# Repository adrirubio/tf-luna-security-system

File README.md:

# TF-Luna Security System
**Full Design Process**: [Blueprint Project](https://blueprint.hackclub.com/projects/7234)

An evolution of my Arduino-based security system that uses a TF-Luna LiDAR sensor to detect when someone passes through a bedroom door, triggering the ESP32-CAM to capture a photo of the intruder.

The system is built around a Freenove ESP32-S3-WROOM-1, which communicates with the TF-Luna over I2C to establish a baseline distance and detect motion. When an intruder is detected, the onboard camera captures an image and sends it to Home Assistant via Wi-Fi. A green LED indicates power status while a red LED flashes to signal an intruder alert. The entire system runs off a power bank and is housed in a custom 3D-printed case mounted with a custom carrier PCB, making it a compact, self-contained DIY security setup with future plans for AI-based person identification.

## Features

- **Intruder Detection:** Real-time motion detection using a TF-Luna LiDAR sensor with a focused 2-degree beam
- **Automatic Photo Capture:** ESP32-CAM captures an image when an intruder is detected passing through the door
- **Home Assistant Integration:** Sends captured images and alerts directly to Home Assistant over Wi-Fi
- **LED Indicators:** Green LED for power status, red LED flashes on intruder detection
- **I2C Communication:** Reliable sensor communication at 100Hz with the TF-Luna
- **Custom PCB:** Single carrier board designed in KiCad and manufactured by JLCPCB
- **Custom 3D Printed Case:** Designed in FreeCAD with mounting pillars and cutouts for all components
- **Power Bank Powered:** Runs off a standard power bank for easy and flexible placement
- **Autonomous Operation:** Runs continuously without manual interaction
- **Future AI Integration:** Planned AI-based identification to recognize the homeowner

## Hardware/BOM

| Component | Qty | Type |
|-----------|-----|------|
| Freenove ESP32-S3-WROOM-1 | 1 | Controller |
| TF-Luna LiDAR Sensor | 1 | LiDAR Sensor |
| microSD Card (32GB) | 1 | Storage |
| Custom Carrier PCB | 1 | PCB |
| Custom 3D Printed Case | 1 | Enclosure |
| Power Bank | 1 | Power |
| USB-A to USB-C Cable | 1 | Cable |
| Mounting Hardware (Assorted Screws) | 1 | Hardware |

## CAD Screenshots

| CAD Assembly (Front View)| CAD Assembly (Top View) |
|--------------------------|-------------------------|
|  |  |

| 3D Case (Front View) | 3D Case (Side View) |
|----------------------|---------------------|
|  |  |

## PCB Screenshots

| PCB Layout |
|-------------------------------|
|  |

| PCB 3D View (Front) | PCB 3D View (Back) |
|----------------------|---------------------|
|  |  |

## Usage
Mount the system above your bedroom door using the 3D-printed case. The TF-Luna LiDAR sensor establishes a baseline distance to the floor and continuously monitors for changes. When someone passes through the doorway, the sensor detects the distance change and triggers the ESP32-CAM to capture a photo. The image is then sent to Home Assistant over Wi-Fi, and the red LED flashes to indicate an intruder was detected. The green LED stays on to confirm the system is powered and running.

## TF-Luna Security System In Action

| Complete Assembly (Side View)|
|------------------------------|
|  |

| Complete Assembly (PCB and Case View) | Complete Assembly (Back View) |
|---------------------------------------|-------------------------------|
|  |  |

### Security System Demo
<a href="https://github.com/adrirubio/tf-luna-security-system/raw/main/demo/video/security-system-demo.mp4">Click here to download the security system demo video (MP4)</a>

### YouTube Demo
[Watch the demo on YouTube](https://youtu.be/43d7Ib5dUhA)

## License

MIT License

---

> GitHub [@adrirubio](https://github.com/adrirubio) &nbsp;&middot;&nbsp;

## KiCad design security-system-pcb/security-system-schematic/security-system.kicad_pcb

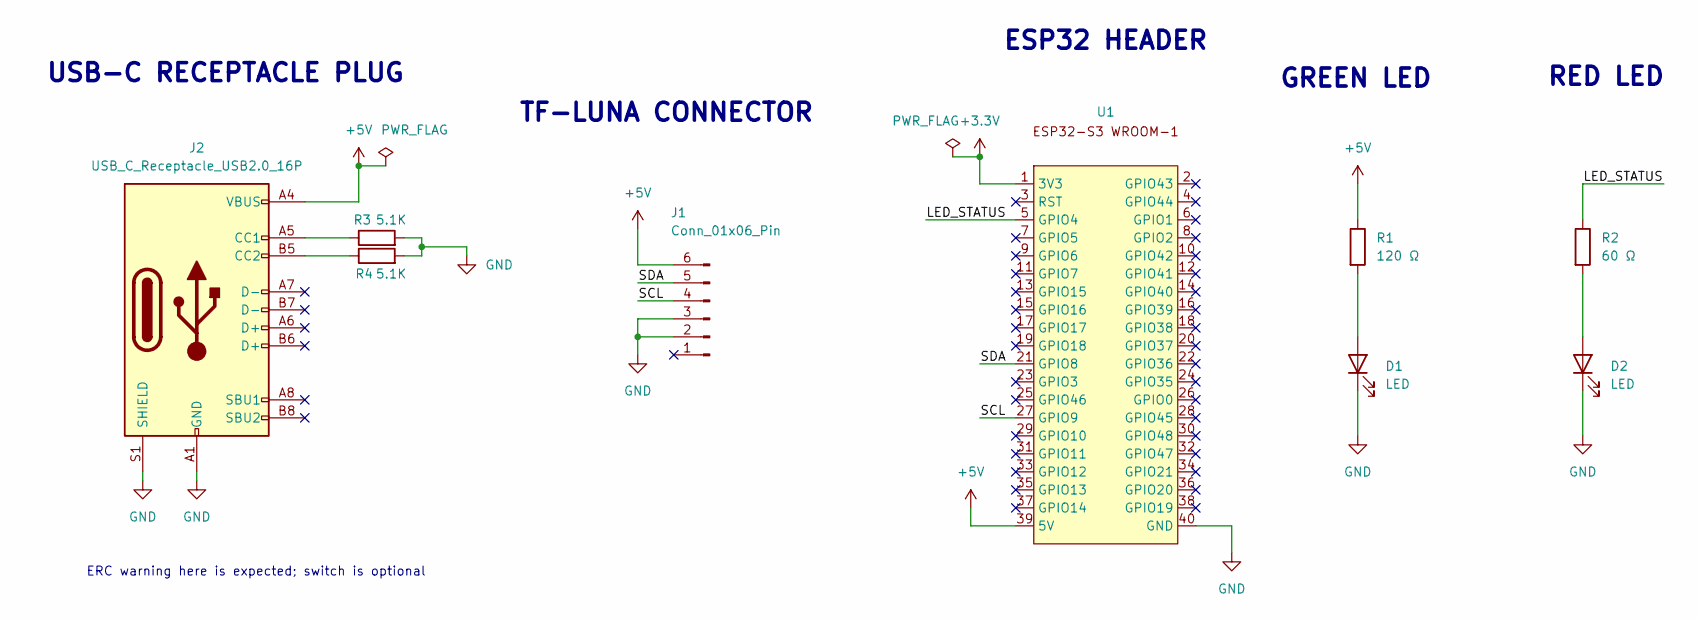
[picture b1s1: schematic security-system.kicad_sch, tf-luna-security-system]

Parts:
D1, D2: LED; LED_D5.0mm
J1: Conn_01x06_Pin; Molex_PicoBlade_53047-0610_1x06_P1.25mm_Vertical
J2: USB_C_Receptacle_USB2.0_16P; USB_C_Receptacle_GCT_USB4105-xx-A_16P_TopMnt_Horizontal
R1: 120 Ω; R_Axial_DIN0207_L6.3mm_D2.5mm_P7.62mm_Horizontal
R2: 60 Ω; R_Axial_DIN0207_L6.3mm_D2.5mm_P7.62mm_Horizontal
R3, R4: 5.1K; R_Axial_DIN0207_L6.3mm_D2.5mm_P7.62mm_Horizontal
U1: ESP32-Header; esp32-header

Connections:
+3.3V: U1.1 (3V3)
+5V: J1.6, J2.A4 (VBUS), J2.A9 (VBUS), J2.B4 (VBUS), J2.B9 (VBUS), R1.1, U1.39 (5V)
/LED_STATUS: R2.1, U1.5 (GPIO4)
/SCL: J1.4, U1.27 (GPIO9)
/SDA: J1.5, U1.21 (GPIO8)
GND: D1.1 (K), D2.1 (K), J1.2, J1.3, J2.A1 (GND), J2.A12 (GND), J2.B1 (GND), J2.B12 (GND), J2.S1 (SHIELD), R3.2, R4.2, U1.40 (GND)
unnamed: D1.2 (A), R1.2
unnamed: D2.2 (A), R2.2
unnamed: J2.A5 (CC1), R3.1
unnamed: J2.B5 (CC2), R4.1

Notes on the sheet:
TF-LUNA CONNECTOR
RED LED
USB-C RECEPTACLE PLUG
ERC warning here is expected; switch is optional
GREEN LED
ESP32 HEADER

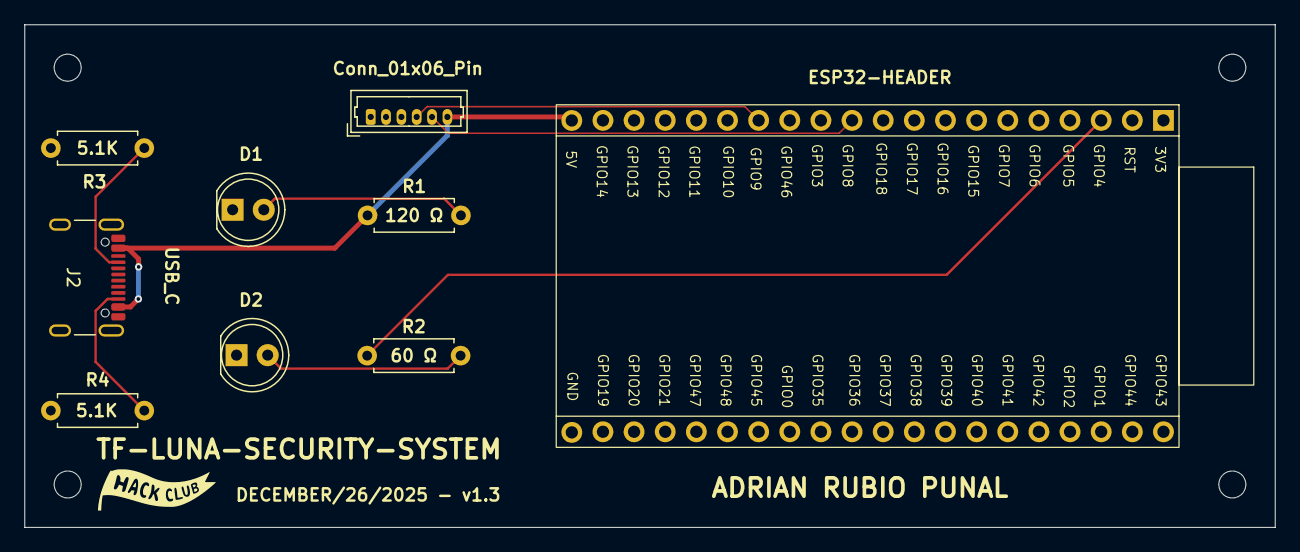
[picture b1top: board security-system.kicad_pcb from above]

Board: 4 copper layers, 102.0 x 41.0 mm, 9 parts (0 on the bottom side), 9 nets.

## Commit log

2025-12-20 Add BOM file
2025-12-20 Rename BOM to CSV
2025-12-20 Push esp32 camera test code
2025-12-22 Add demo picture and pcb schematic
2025-12-26 Add PCB changes
2025-12-29 Add PCB changes and 3D case
2025-12-30 Add updated gerbers
2026-01-01 Push PCB version 1.3
2026-01-01 Made small changes
2026-01-02 Changes to the 3D case
2026-01-03 Changes to the schematic and case
2026-01-05 Push changes to case and gerbers v1.4
2026-01-10 3D case changes
2026-03-01 Add STEP files
2026-03-28 Add security system in action images
2026-03-28 Minor change to README
2026-03-30 Add tf-luna test code and project code
2026-04-07 Minor change to bom.csv
2026-04-07 Add project demo
2026-04-07 Fix small README mistake
2026-04-12 Update web app
2026-04-13 Add demo video and update readme with video download and youtube video likns
2026-04-13 Add missing screenshot
2026-04-13 Add working link
2026-04-13 Add correct text for link
